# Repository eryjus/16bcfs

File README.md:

# 16-Bit Computer From Scratch

This repository contains the complete works associated with the 16-Bit Computer From Scrath (16bcfs) project.

---

## Videos

I am documenting my 16-Bit Computer build in video form.  You can find the entire playlist [here](https://www.youtube.com/playlist?list=PLUF7WfBe0k3g9wpTtg41QP3jl5y8T1aGV).

---

## License

See [LICENSE.md](LICENSE.md).

---

## Build System

I use `tup` as my primary build system.  I usually will wrap `tup` in `make` commands.  You can find `tup` [here](https://gittup.org/tup/).  I simply find `tup` to more reliable detect changed sources with less work.

### Qt6_DIR Environment Variable

The `Qt6_DIR` Environment Variable needs to point to the installation location of Qt6, for example `~/Qt/6.6.0/gcc_64/`.  Your installation location may be different, so copy-and-paste is not advised.

---

## EEPROM Programmer

I do not have a commercial EEPROM programmer.  I use the TommyPROM programmer.  You can find all the relevant information on TommyPROM [here](https://tomnisbet.github.io/TommyPROM/).  In Linux, I use `minicom` as the interface.  Hint: use `sudo minicom -s` to set up the defaults.

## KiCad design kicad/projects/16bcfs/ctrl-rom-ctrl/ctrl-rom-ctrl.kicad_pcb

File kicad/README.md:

# 16-Bit Computer From Scratch KiCad Library

This folder contains the KiCad files used in designing the PCBs.

---

## Videos

I am documenting my 16-Bit Computer build in video form.  You can find the entire playlist [here](https://www.youtube.com/playlist?list=PLUF7WfBe0k3g9wpTtg41QP3jl5y8T1aGV).

---

## License

See [LICENSE.md](../LICENSE.md).

---

## Fitness

Please understand that I do not represent or warranty that these schematics and PCB designs are fit for any purpose including the project for which they were intended.  I would hate for you to invest your own hard-earned money into something that may or may not work for you.  However, you are free to do what you wish with this stuff as stated in the [license](../LICENSE.md).  Just have fun with it.

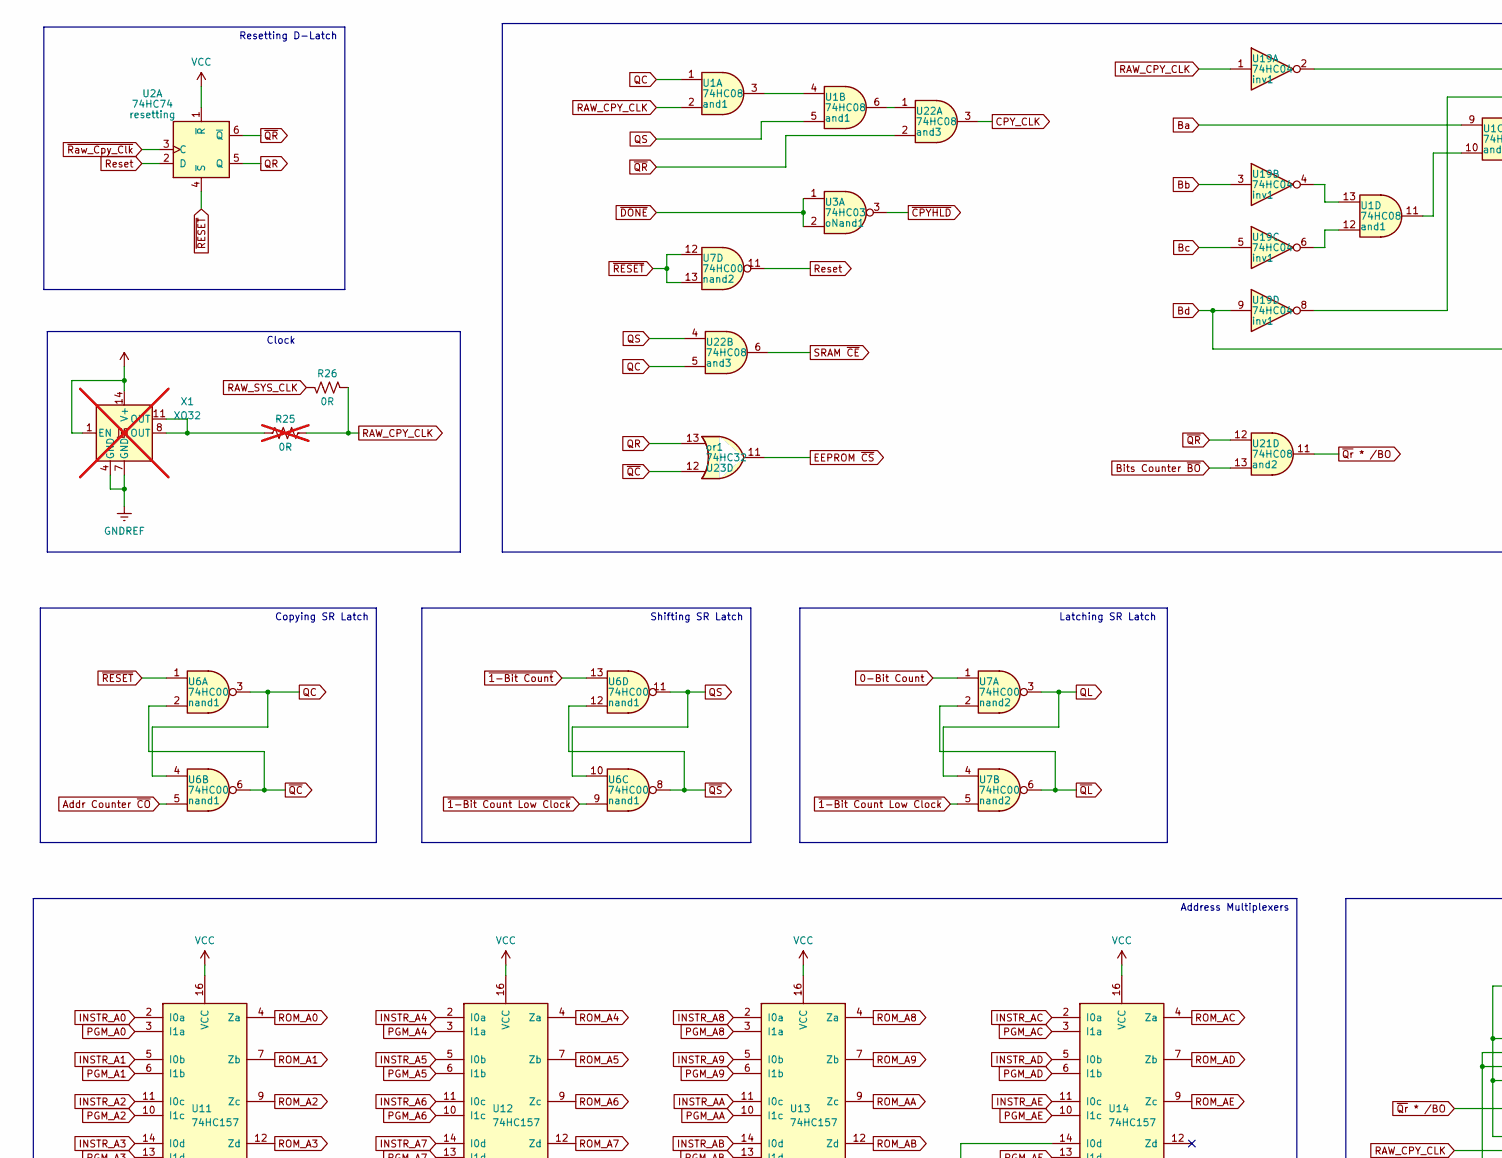
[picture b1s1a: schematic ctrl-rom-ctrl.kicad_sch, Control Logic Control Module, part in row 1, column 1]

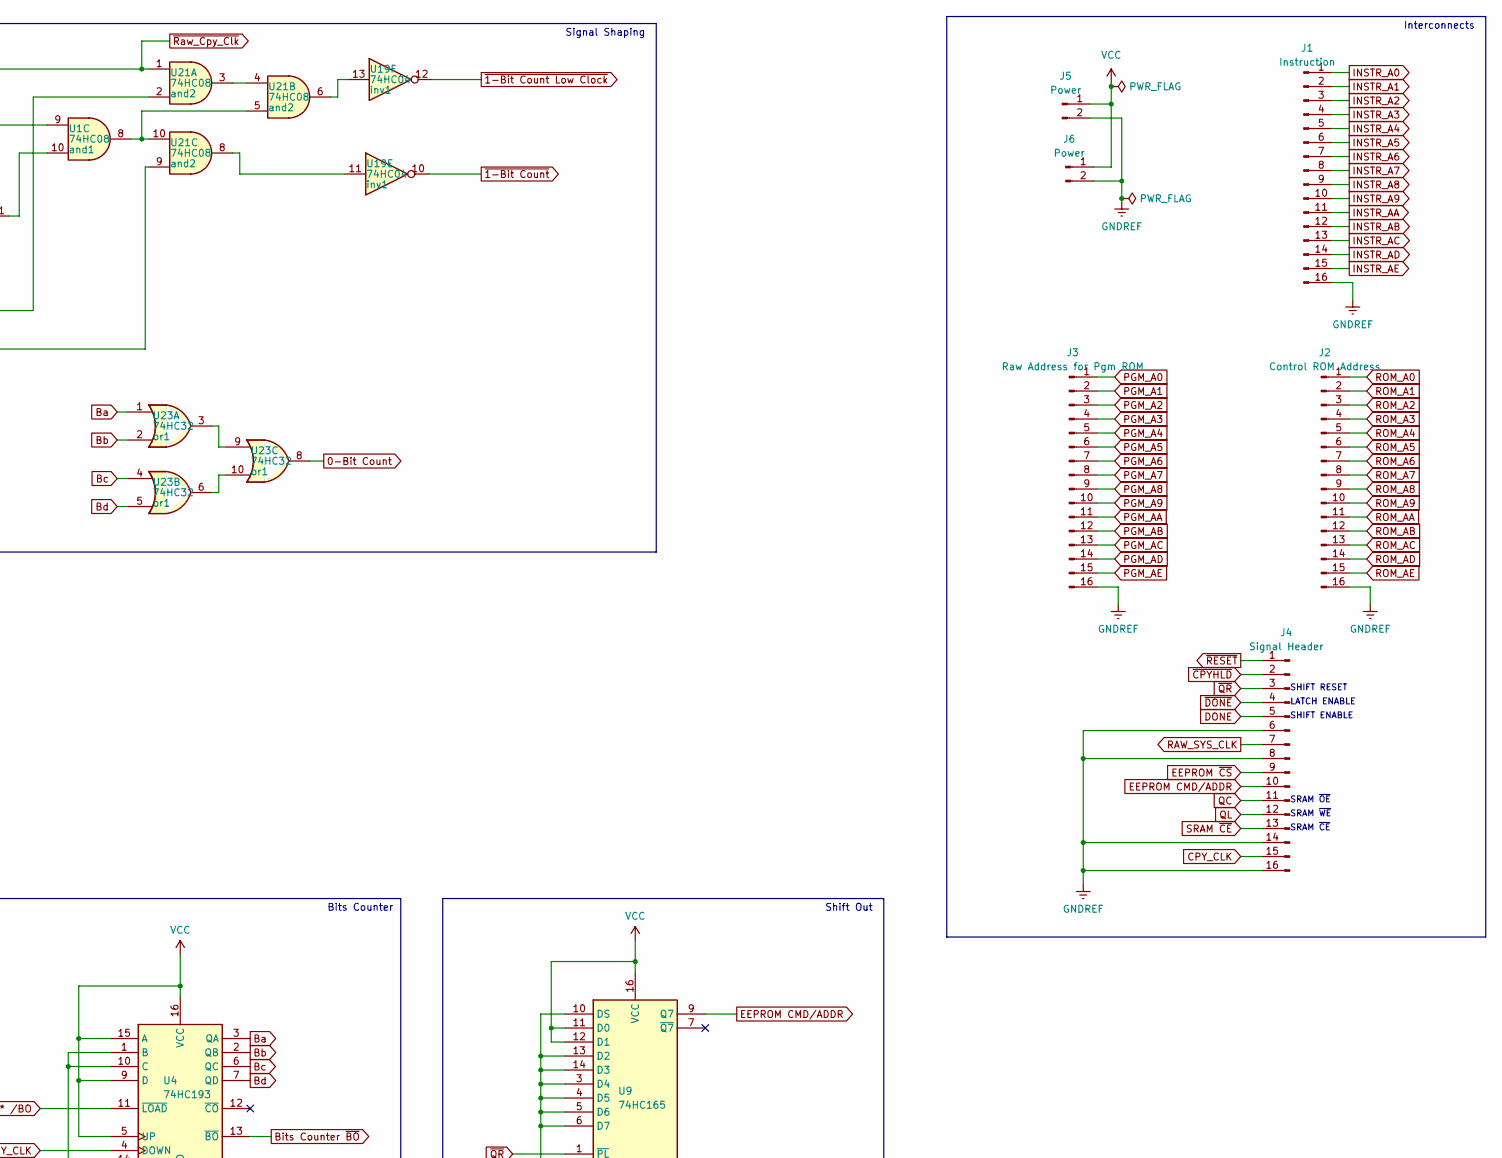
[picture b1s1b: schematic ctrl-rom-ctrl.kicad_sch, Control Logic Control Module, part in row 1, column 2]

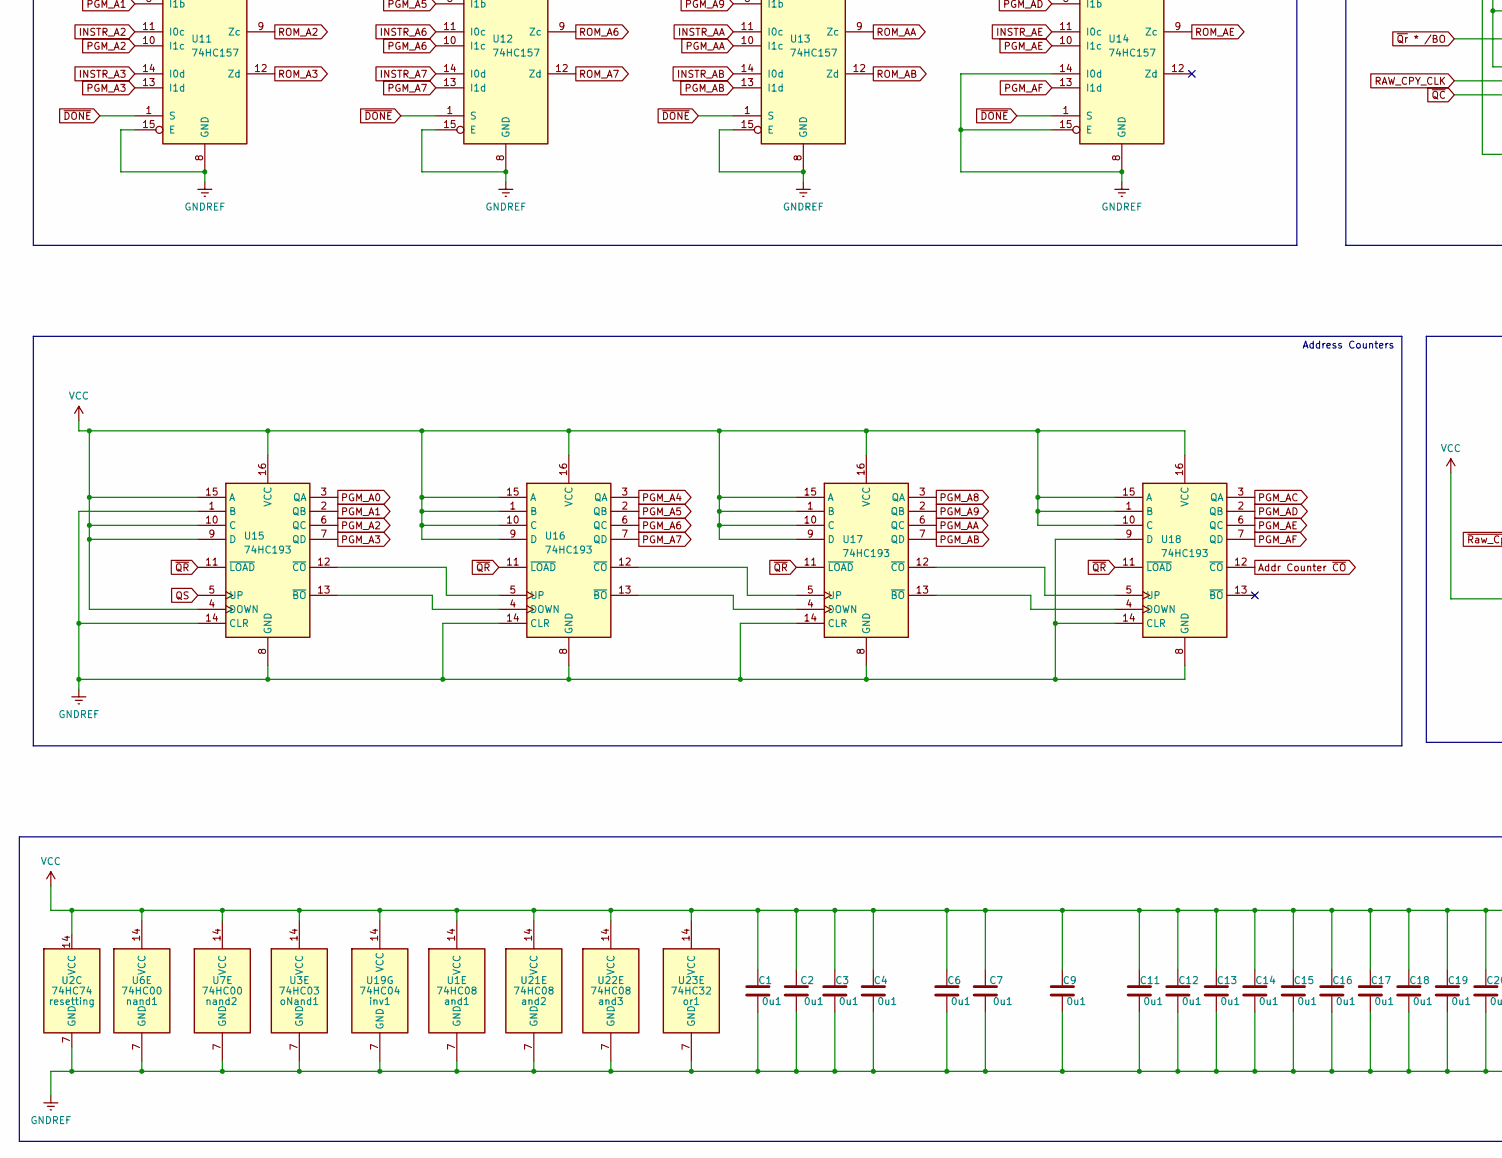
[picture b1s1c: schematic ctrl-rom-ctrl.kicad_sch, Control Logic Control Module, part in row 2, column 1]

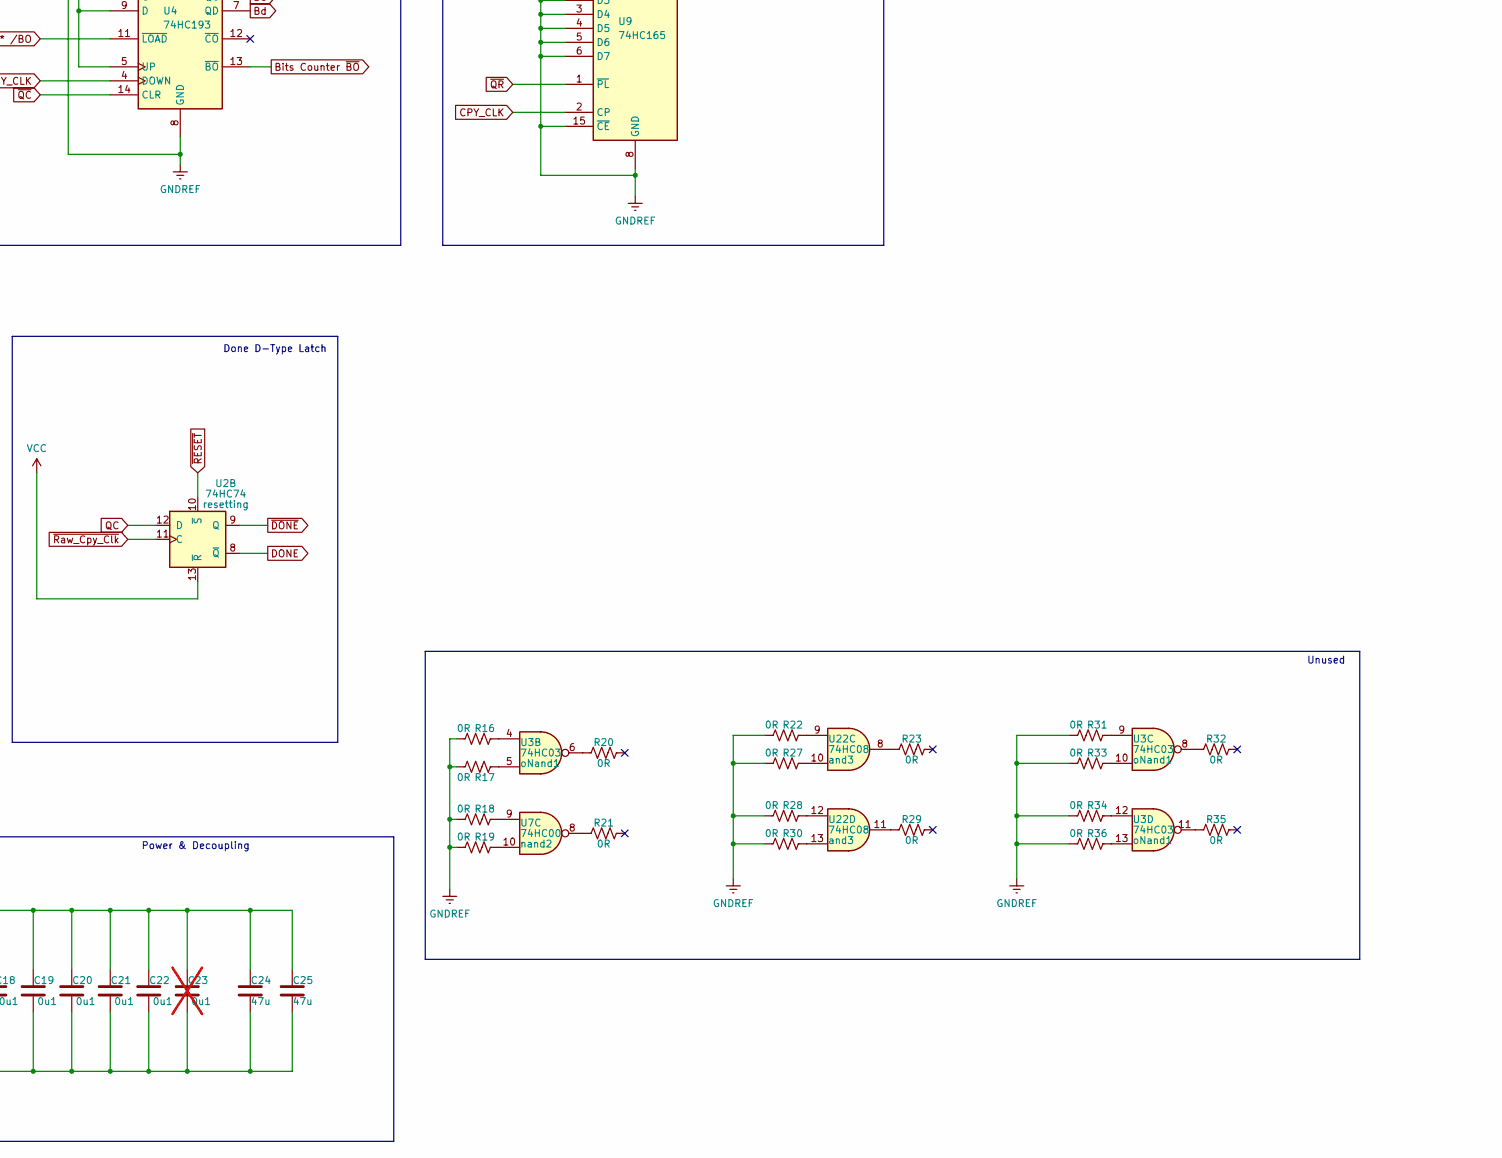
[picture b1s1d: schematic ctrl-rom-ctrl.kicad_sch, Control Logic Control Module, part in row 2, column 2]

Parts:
C1, C2, C3, C4, C6, C7, C9, C11, C12, C13, C14, C15, C16, C17, C18, C19, C20, C21, C22: 0u1; C_1206_3216Metric_Pad1.33x1.80mm_HandSolder
C23: 0u1; C_1206_3216Metric_Pad1.33x1.80mm_HandSolder; not fitted
C24, C25: 47u; C_1206_3216Metric_Pad1.33x1.80mm_HandSolder
J1: Instruction; PinHeader_1x16_P2.54mm_Vertical
J2: Control ROM Address; PinHeader_1x16_P2.54mm_Vertical
J3: Raw Address for Pgm ROM; PinHeader_1x16_P2.54mm_Vertical
J4: Signal Header; PinHeader_1x16_P2.54mm_Vertical
J5, J6: Power; PinHeader_1x02_P2.54mm_Vertical
R16, R17, R18, R19, R20, R21, R22, R23, R26, R27, R28, R29, R30, R31, R32, R33, R34, R35, R36: 0R; R_1206_3216Metric_Pad1.30x1.75mm_HandSolder
R25: 0R; R_1206_3216Metric_Pad1.30x1.75mm_HandSolder; not fitted
U1, U21, U22: 74HC08; SOIC-14_3.9x8.7mm_P1.27mm
U2: 74HC74; SOIC-14_3.9x8.7mm_P1.27mm
U3: 74HC03; SOIC-14_3.9x8.7mm_P1.27mm
U4, U15, U16, U17, U18: 74HC193; SOIC-16_3.9x9.9mm_P1.27mm
U6, U7: 74HC00; SOIC-14_3.9x8.7mm_P1.27mm
U9: 74HC165; SOIC-16_3.9x9.9mm_P1.27mm
U11, U12, U13, U14: 74HC157; SOIC-16_3.9x9.9mm_P1.27mm
U19: 74HC04; SOIC-14_3.9x8.7mm_P1.27mm
U23: 74HC32; SOIC-14_3.9x8.7mm_P1.27mm
X1: XO32; Oscillator_DIP-8-14; not fitted

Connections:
0-Bit Count: U7.1, U23.8
Addr Counter ~CO: U6.5, U18.12 (~CO)
Ba: U1.9, U4.3 (QA), U23.1
Bb: U4.2 (QB), U19.3, U23.2
Bc: U4.6 (QC), U19.5, U23.4
Bd: U4.7 (QD), U19.9, U21.9, U23.5
Bits Counter ~BO: U4.13 (~BO), U21.13
CPY_CLK: J4.15, U9.2 (CP), U22.3
DONE: J4.5, U2.8 (~Q)
EEPROM CMD/ADDR: J4.10, U9.9 (Q7)
EEPROM ~CS: J4.9, U23.11
GNDREF: C1.2, C2.2, C3.2, C4.2, C6.2, C7.2, C9.2, C11.2, C12.2, C13.2, C14.2, C15.2, C16.2, C17.2, C18.2, C19.2, C20.2, C21.2, C22.2, C23.2, C24.2, C25.2, J1.16, J2.16, J3.16, J4.6, J4.8, J4.14, J4.16, J5.2, J6.2, R16.1, R17.1, R18.1, R19.1, R22.1, R27.1, R28.1, R30.1, R31.1, R33.1, R34.1, R36.1, U1.7 (GND), U2.7 (GND), U3.7 (GND), U4.1 (B), U4.8 (GND), U4.10 (C), U6.7 (GND), U7.7 (GND), U9.3 (D4), U9.4 (D5), U9.5 (D6), U9.6 (D7), U9.8 (GND), U9.10 (DS), U9.13 (D2), U9.14 (D3), U9.15 (~CE), U11.8 (GND), U11.15 (E), U12.8 (GND), U12.15 (E), U13.8 (GND), U13.15 (E), U14.8 (GND), U14.14 (I0d), U14.15 (E), U15.1 (B), U15.8 (GND), U15.14 (CLR), U16.8 (GND), U16.14 (CLR), U17.8 (GND), U17.14 (CLR), U18.8 (GND), U18.9 (D), U18.14 (CLR), U19.7 (GND), U21.7 (GND), U22.7 (GND), U23.7 (GND), X1.4 (GND), X1.7 (GND)
INSTR_A0: J1.1, U11.2 (I0a)
INSTR_A1: J1.2, U11.5 (I0b)
INSTR_A2: J1.3, U11.11 (I0c)
INSTR_A3: J1.4, U11.14 (I0d)
INSTR_A4: J1.5, U12.2 (I0a)
INSTR_A5: J1.6, U12.5 (I0b)
INSTR_A6: J1.7, U12.11 (I0c)
INSTR_A7: J1.8, U12.14 (I0d)
INSTR_A8: J1.9, U13.2 (I0a)
INSTR_A9: J1.10, U13.5 (I0b)
INSTR_AA: J1.11, U13.11 (I0c)
INSTR_AB: J1.12, U13.14 (I0d)
INSTR_AC: J1.13, U14.2 (I0a)
INSTR_AD: J1.14, U14.5 (I0b)
INSTR_AE: J1.15, U14.11 (I0c)
unnamed: R16.2, U3.4
unnamed: R17.2, U3.5
unnamed: R18.2, U7.9
unnamed: R19.2, U7.10
unnamed: R20.1, U3.6
unnamed: R21.1, U7.8
unnamed: R22.2, U22.9
unnamed: R23.1, U22.8
unnamed: R25.1, X1.8 (OUT), X1.11 (OUT)
unnamed: R27.2, U22.10
unnamed: R28.2, U22.12
unnamed: R29.1, U22.11
unnamed: R30.2, U22.13
unnamed: R31.2, U3.9
unnamed: R32.1, U3.8
unnamed: R33.2, U3.10
unnamed: R34.2, U3.12
unnamed: R35.1, U3.11
unnamed: R36.2, U3.13
unnamed: U1.3, U1.4
unnamed: U1.6, U22.1
unnamed: U1.8, U21.5, U21.10
unnamed: U1.10, U1.11
unnamed: U1.12, U19.6
unnamed: U1.13, U19.4
unnamed: U15.13 (~BO), U16.4 (DOWN)
unnamed: U15.12 (~CO), U16.5 (UP)
unnamed: U16.13 (~BO), U17.4 (DOWN)
unnamed: U16.12 (~CO), U17.5 (UP)
unnamed: U17.13 (~BO), U18.4 (DOWN)
unnamed: U17.12 (~CO), U18.5 (UP)
unnamed: U19.8, U21.2
unnamed: U19.11, U21.8
unnamed: U19.13, U21.6
unnamed: U21.3, U21.4
unnamed: U23.3, U23.9
unnamed: U23.6, U23.10
PGM_A0: J3.1, U11.3 (I1a), U15.3 (QA)
PGM_A1: J3.2, U11.6 (I1b), U15.2 (QB)
PGM_A2: J3.3, U11.10 (I1c), U15.6 (QC)
PGM_A3: J3.4, U11.13 (I1d), U15.7 (QD)
PGM_A4: J3.5, U12.3 (I1a), U16.3 (QA)
PGM_A5: J3.6, U12.6 (I1b), U16.2 (QB)
PGM_A6: J3.7, U12.10 (I1c), U16.6 (QC)
PGM_A7: J3.8, U12.13 (I1d), U16.7 (QD)
PGM_A8: J3.9, U13.3 (I1a), U17.3 (QA)
PGM_A9: J3.10, U13.6 (I1b), U17.2 (QB)
PGM_AA: J3.11, U13.10 (I1c), U17.6 (QC)
PGM_AB: J3.12, U13.13 (I1d), U17.7 (QD)
PGM_AC: J3.13, U14.3 (I1a), U18.3 (QA)
PGM_AD: J3.14, U14.6 (I1b), U18.2 (QB)
PGM_AE: J3.15, U14.10 (I1c), U18.6 (QC)
PGM_AF: U14.13 (I1d), U18.7 (QD)
QC: J4.11, U1.1, U2.12 (D), U6.3, U6.4, U22.5
QL: J4.12, U7.3, U7.4
QR: U2.5 (Q), U23.13
QS: U1.5, U6.10, U6.11, U15.5 (UP), U22.4
RAW_CPY_CLK: R25.2, R26.1, U1.2, U4.4 (DOWN), U19.1
RAW_SYS_CLK: J4.7, R26.2
ROM_A0: J2.1, U11.4 (Za)
ROM_A1: J2.2, U11.7 (Zb)
ROM_A2: J2.3, U11.9 (Zc)
ROM_A3: J2.4, U11.12 (Zd)
ROM_A4: J2.5, U12.4 (Za)
ROM_A5: J2.6, U12.7 (Zb)
ROM_A6: J2.7, U12.9 (Zc)
ROM_A7: J2.8, U12.12 (Zd)
ROM_A8: J2.9, U13.4 (Za)
ROM_A9: J2.10, U13.7 (Zb)
ROM_AA: J2.11, U13.9 (Zc)
ROM_AB: J2.12, U13.12 (Zd)
ROM_AC: J2.13, U14.4 (Za)
ROM_AD: J2.14, U14.7 (Zb)
ROM_AE: J2.15, U14.9 (Zc)
Reset: U2.2 (D), U7.11
SRAM ~CE: J4.13, U22.6
VCC: C1.1, C2.1, C3.1, C4.1, C6.1, C7.1, C9.1, C11.1, C12.1, C13.1, C14.1, C15.1, C16.1, C17.1, C18.1, C19.1, C20.1, C21.1, C22.1, C23.1, C24.1, C25.1, J5.1, J6.1, U1.14 (VCC), U2.1 (~R), U2.13 (~R), U2.14 (VCC), U3.14 (VCC), U4.5 (UP), U4.9 (D), U4.15 (A), U4.16 (VCC), U6.14 (VCC), U7.14 (VCC), U9.11 (D0), U9.12 (D1), U9.16 (VCC), U11.16 (VCC), U12.16 (VCC), U13.16 (VCC), U14.16 (VCC), U15.4 (DOWN), U15.9 (D), U15.10 (C), U15.15 (A), U15.16 (VCC), U16.1 (B), U16.9 (D), U16.10 (C), U16.15 (A), U16.16 (VCC), U17.1 (B), U17.9 (D), U17.10 (C), U17.15 (A), U17.16 (VCC), U18.1 (B), U18.10 (C), U18.15 (A), U18.16 (VCC), U19.14 (VCC), U21.14 (VCC), U22.14 (VCC), U23.14 (VCC), X1.1 (EN), X1.14 (V+)
~1-Bit Count Low Clock: U6.9, U7.5, U19.12
~1-Bit Count: U6.13, U19.10
~CPYHLD: J4.2, U3.3
~DONE: J4.4, U2.9 (Q), U3.1, U3.2, U11.1 (S), U12.1 (S), U13.1 (S), U14.1 (S)
~QC: U4.14 (CLR), U6.2, U6.6, U23.12
~QL: U7.2, U7.6
~QR: J4.3, U2.6 (~Q), U9.1 (~PL), U15.11 (~LOAD), U16.11 (~LOAD), U17.11 (~LOAD), U18.11 (~LOAD), U21.12, U22.2
~QS: U6.8, U6.12
~Qr * /BO: U4.11 (~LOAD), U21.11
~RESET: J4.1, U2.4 (~S), U2.10 (~S), U6.1, U7.12, U7.13
~Raw_Cpy_Clk: U2.3 (C), U2.11 (C), U19.2, U21.1

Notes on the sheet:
SHIFT RESET
Shift Out
Shifting SR Latch
Resetting D-Latch
LATCH ENABLE
Clock
SRAM ~{CE}
SRAM ~{WE}
Bits Counter
Unused
Power & Decoupling
Copying SR Latch
SRAM ~{OE}
Address Multiplexers
Done D-Type Latch
SHIFT ENABLE
Address Counters
Signal Shaping
Interconnects
Latching SR Latch

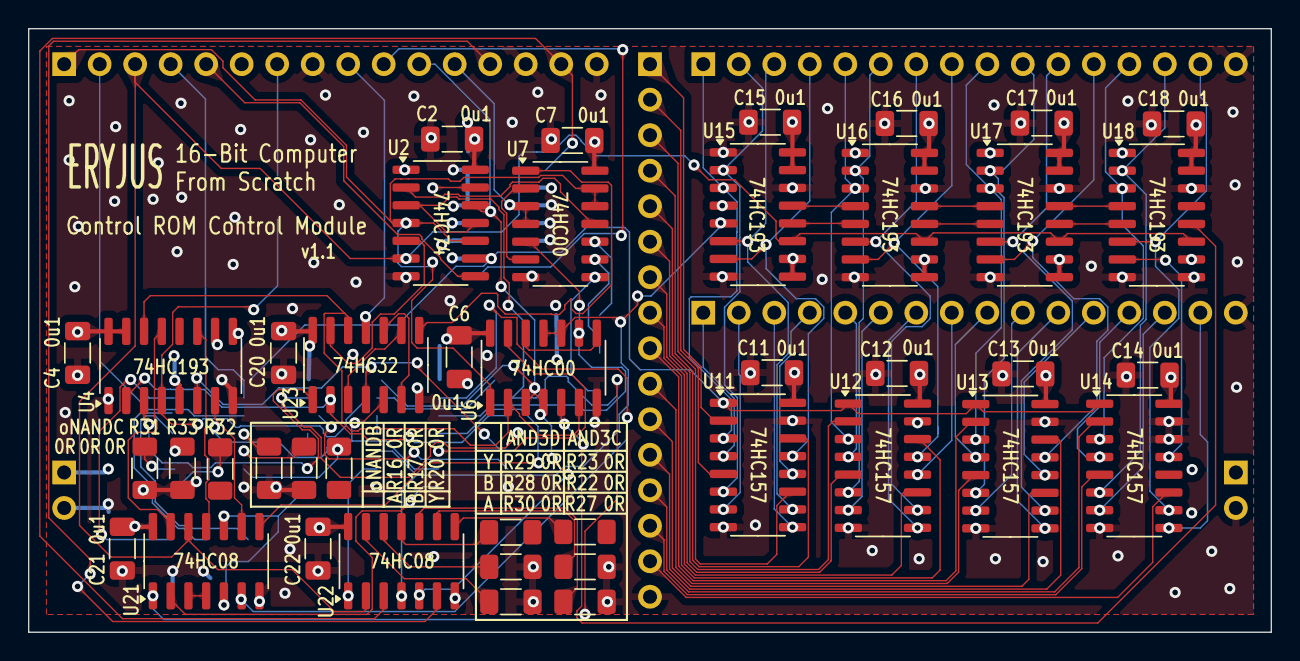
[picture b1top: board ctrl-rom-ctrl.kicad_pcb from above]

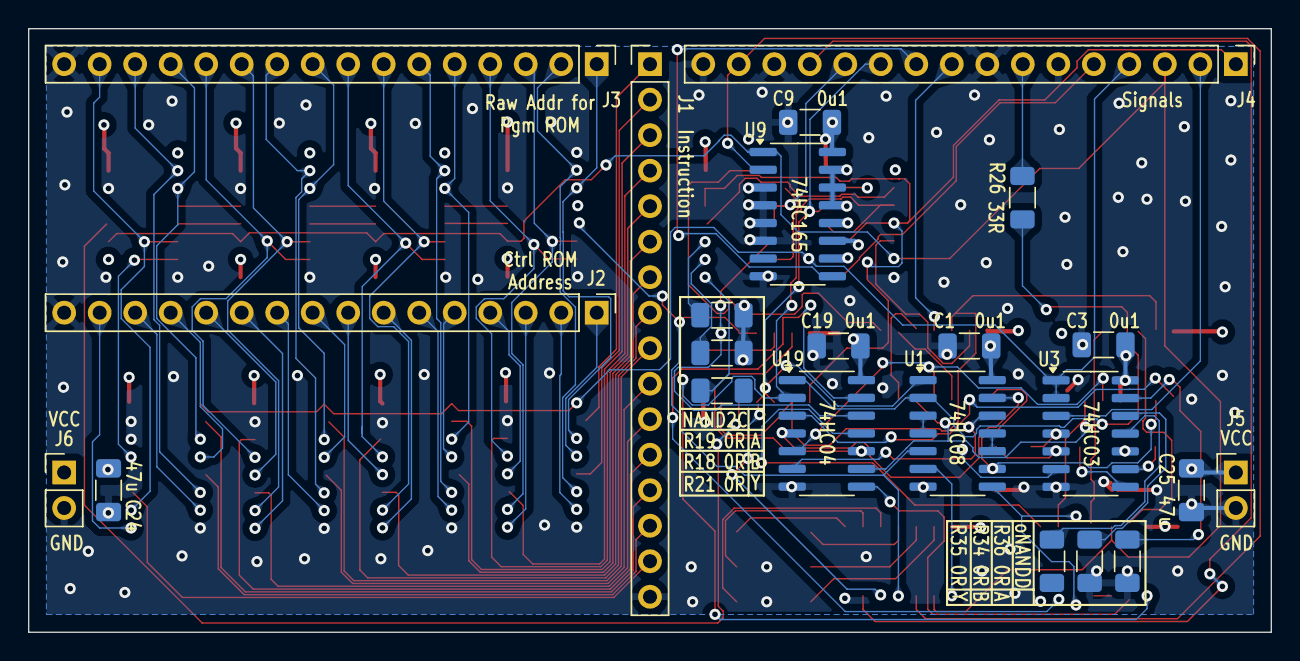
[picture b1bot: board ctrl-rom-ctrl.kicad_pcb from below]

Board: 4 copper layers, 88.9 x 43.2 mm, 65 parts (23 on the bottom side), 114 nets.

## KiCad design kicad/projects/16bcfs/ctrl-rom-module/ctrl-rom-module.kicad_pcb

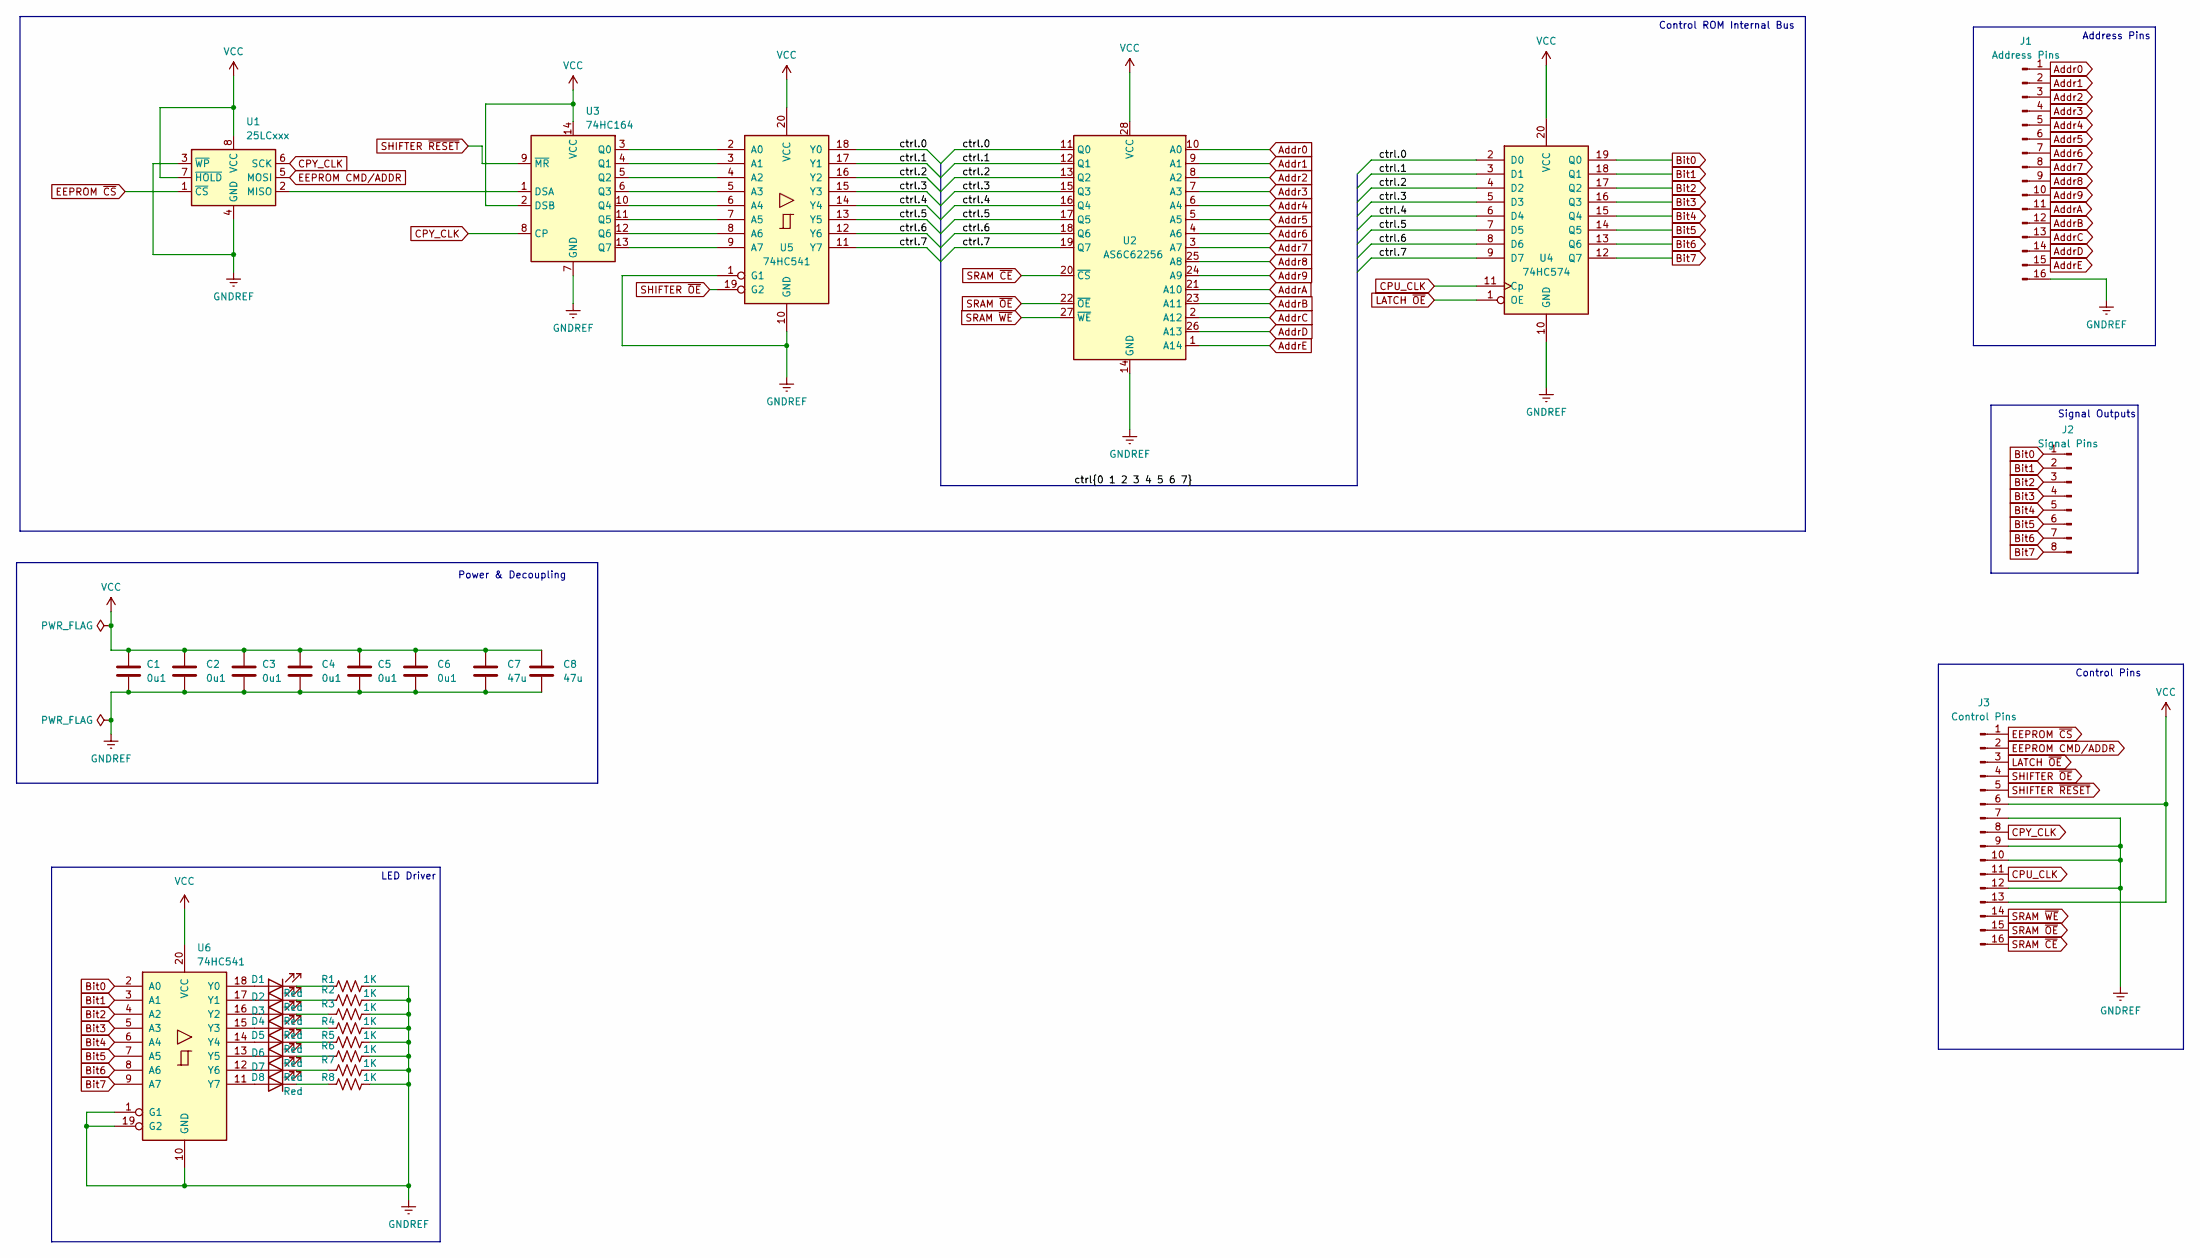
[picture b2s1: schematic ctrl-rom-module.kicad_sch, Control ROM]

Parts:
C1, C2, C3, C4, C5, C6: 0u1; C_1206_3216Metric_Pad1.33x1.80mm_HandSolder
C7, C8: 47u; C_1206_3216Metric_Pad1.33x1.80mm_HandSolder
D1, D2, D3, D4, D5, D6, D7, D8: Red; LED_1206_3216Metric_Pad1.42x1.75mm_HandSolder
J1: Address Pins; PinHeader_1x16_P2.54mm_Vertical
J2: Signal Pins; PinHeader_1x08_P2.54mm_Vertical
J3: Control Pins; PinHeader_1x16_P2.54mm_Vertical
R1, R2, R3, R4, R5, R6, R7, R8: 1K; R_1206_3216Metric_Pad1.30x1.75mm_HandSolder
U1: 25LCxxx; DIP-8_W7.62mm_Socket
U2: AS6C62256; SOP-28_MIL330_ALL
U3: 74HC164; SOIC-14_3.9x8.7mm_P1.27mm
U4: 74HC574; SOIC-20W_7.5x12.8mm_P1.27mm
U5, U6: 74HC541; SOIC-20W_7.5x12.8mm_P1.27mm

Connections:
/ctrl.0: U2.11 (Q0), U4.2 (D0), U5.18 (Y0)
/ctrl.1: U2.12 (Q1), U4.3 (D1), U5.17 (Y1)
/ctrl.2: U2.13 (Q2), U4.4 (D2), U5.16 (Y2)
/ctrl.3: U2.15 (Q3), U4.5 (D3), U5.15 (Y3)
/ctrl.4: U2.16 (Q4), U4.6 (D4), U5.14 (Y4)
/ctrl.5: U2.17 (Q5), U4.7 (D5), U5.13 (Y5)
/ctrl.6: U2.18 (Q6), U4.8 (D6), U5.12 (Y6)
/ctrl.7: U2.19 (Q7), U4.9 (D7), U5.11 (Y7)
Addr0: J1.1, U2.10 (A0)
Addr1: J1.2, U2.9 (A1)
Addr2: J1.3, U2.8 (A2)
Addr3: J1.4, U2.7 (A3)
Addr4: J1.5, U2.6 (A4)
Addr5: J1.6, U2.5 (A5)
Addr6: J1.7, U2.4 (A6)
Addr7: J1.8, U2.3 (A7)
Addr8: J1.9, U2.25 (A8)
Addr9: J1.10, U2.24 (A9)
AddrA: J1.11, U2.21 (A10)
AddrB: J1.12, U2.23 (A11)
AddrC: J1.13, U2.2 (A12)
AddrD: J1.14, U2.26 (A13)
AddrE: J1.15, U2.1 (A14)
Bit0: J2.1, U4.19 (Q0), U6.2 (A0)
Bit1: J2.2, U4.18 (Q1), U6.3 (A1)
Bit2: J2.3, U4.17 (Q2), U6.4 (A2)
Bit3: J2.4, U4.16 (Q3), U6.5 (A3)
Bit4: J2.5, U4.15 (Q4), U6.6 (A4)
Bit5: J2.6, U4.14 (Q5), U6.7 (A5)
Bit6: J2.7, U4.13 (Q6), U6.8 (A6)
Bit7: J2.8, U4.12 (Q7), U6.9 (A7)
CPU_CLK: J3.11, U4.11 (Cp)
CPY_CLK: J3.8, U1.6 (SCK), U3.8 (CP)
EEPROM CMD/ADDR: J3.2, U1.5 (MOSI)
EEPROM ~CS: J3.1, U1.1 (~CS)
GNDREF: C1.2, C2.2, C3.2, C4.2, C5.2, C6.2, C7.2, C8.2, J1.16, J3.7, J3.9, J3.10, J3.12, R1.2, R2.2, R3.2, R4.2, R5.2, R6.2, R7.2, R8.2, U1.3 (~WP), U1.4 (GND), U2.14 (GND), U3.7 (GND), U4.10 (GND), U5.1 (G1), U5.10 (GND), U6.1 (G1), U6.10 (GND), U6.19 (G2)
LATCH ~OE: J3.3, U4.1 (OE)
unnamed: D1.2 (A), U6.18 (Y0)
unnamed: D1.1 (K), R1.1
unnamed: D2.2 (A), U6.17 (Y1)
unnamed: D2.1 (K), R2.1
unnamed: D3.2 (A), U6.16 (Y2)
unnamed: D3.1 (K), R3.1
unnamed: D4.2 (A), U6.15 (Y3)
unnamed: D4.1 (K), R4.1
unnamed: D5.2 (A), U6.14 (Y4)
unnamed: D5.1 (K), R5.1
unnamed: D6.2 (A), U6.13 (Y5)
unnamed: D6.1 (K), R6.1
unnamed: D7.2 (A), U6.12 (Y6)
unnamed: D7.1 (K), R7.1
unnamed: D8.2 (A), U6.11 (Y7)
unnamed: D8.1 (K), R8.1
unnamed: U1.2 (MISO), U3.1 (DSA)
unnamed: U3.3 (Q0), U5.2 (A0)
unnamed: U3.4 (Q1), U5.3 (A1)
unnamed: U3.5 (Q2), U5.4 (A2)
unnamed: U3.6 (Q3), U5.5 (A3)
unnamed: U3.10 (Q4), U5.6 (A4)
unnamed: U3.11 (Q5), U5.7 (A5)
unnamed: U3.12 (Q6), U5.8 (A6)
unnamed: U3.13 (Q7), U5.9 (A7)
SHIFTER ~OE: J3.4, U5.19 (G2)
SHIFTER ~RESET: J3.5, U3.9 (~MR)
SRAM ~CE: J3.16, U2.20 (~CS)
SRAM ~OE: J3.15, U2.22 (~OE)
SRAM ~WE: J3.14, U2.27 (~WE)
VCC: C1.1, C2.1, C3.1, C4.1, C5.1, C6.1, C7.1, C8.1, J3.6, J3.13, U1.7 (~HOLD), U1.8 (VCC), U2.28 (VCC), U3.2 (DSB), U3.14 (VCC), U4.20 (VCC), U5.20 (VCC), U6.20 (VCC)

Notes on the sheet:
Control ROM Internal Bus
Address Pins
Signal Outputs
Power & Decoupling
Control Pins
LED Driver

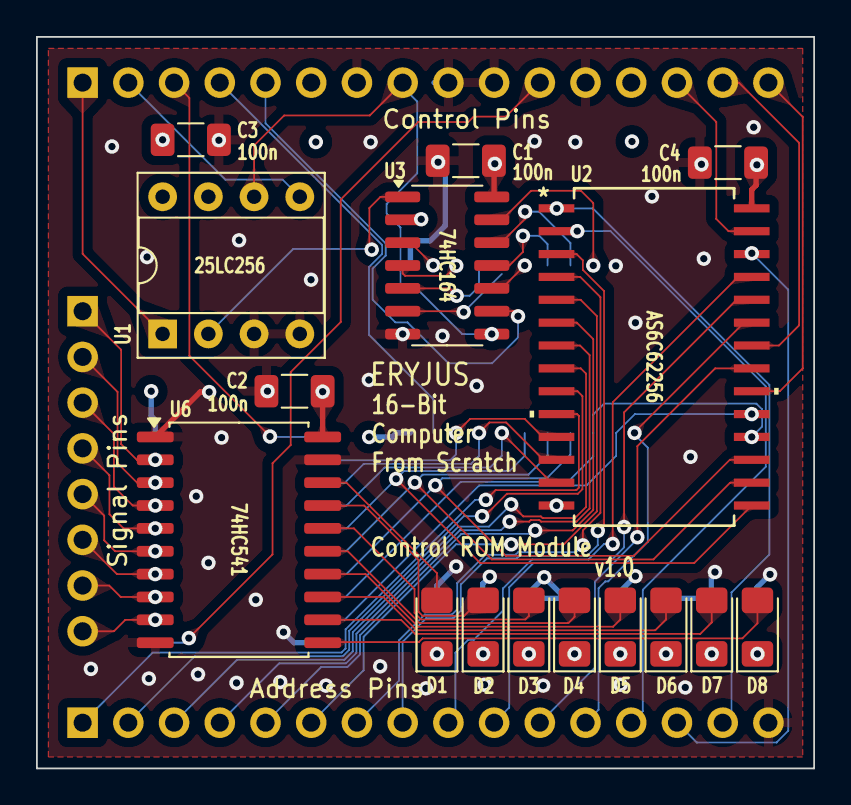
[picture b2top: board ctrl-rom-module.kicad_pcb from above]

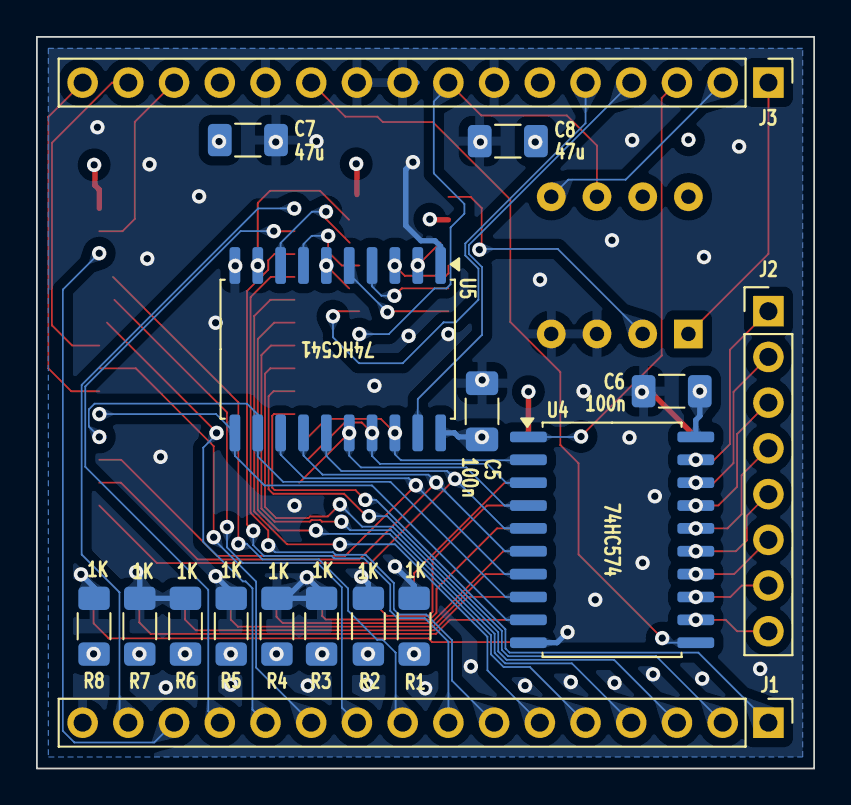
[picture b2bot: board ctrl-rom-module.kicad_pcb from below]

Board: 4 copper layers, 43.2 x 40.6 mm, 33 parts (17 on the bottom side), 68 nets.

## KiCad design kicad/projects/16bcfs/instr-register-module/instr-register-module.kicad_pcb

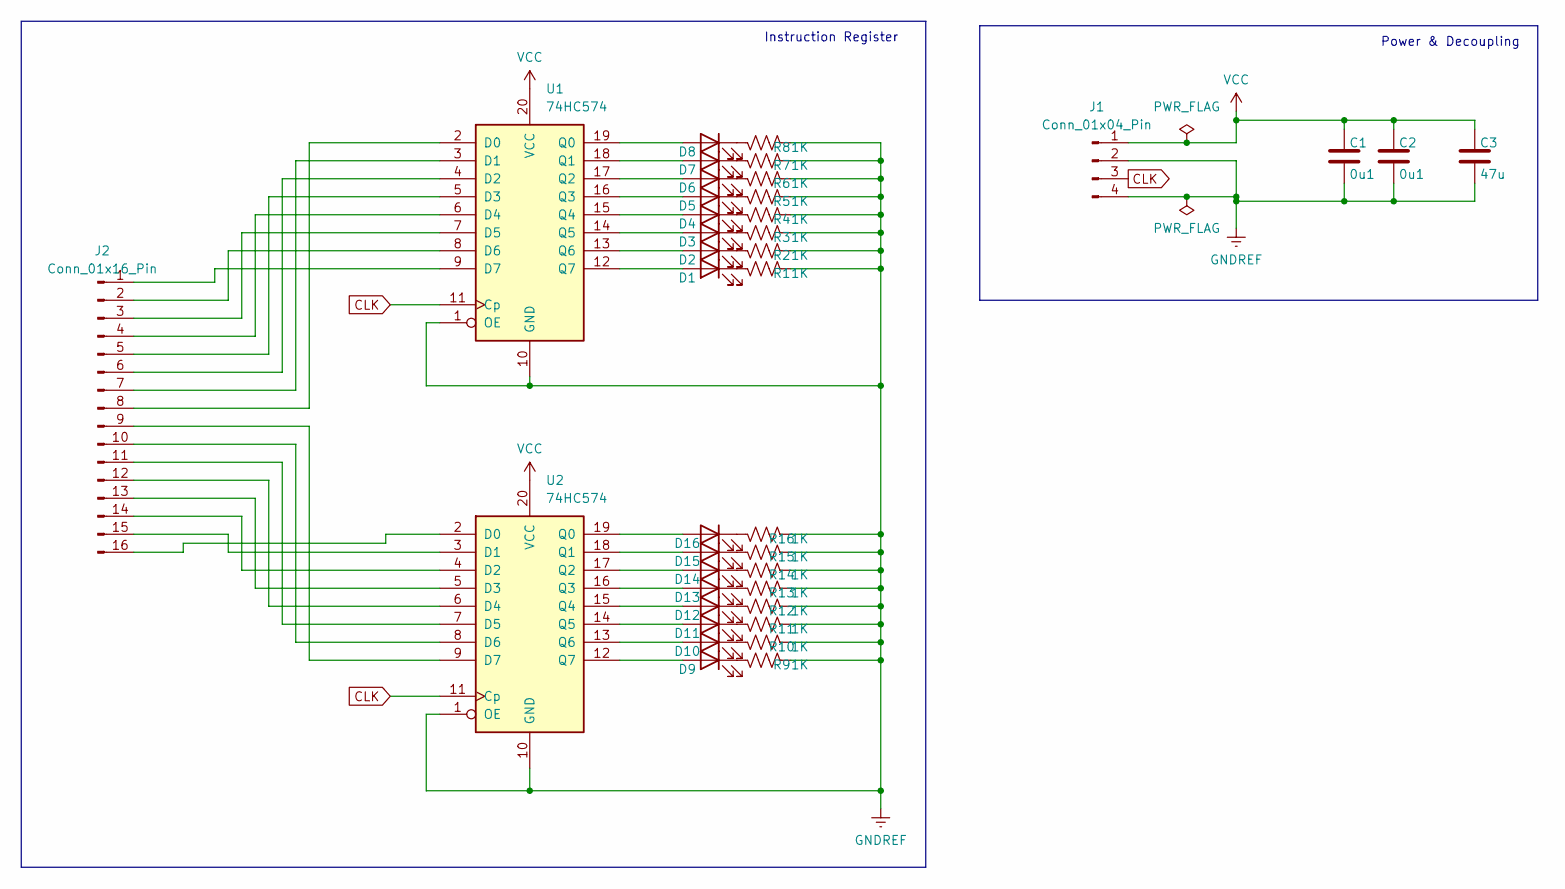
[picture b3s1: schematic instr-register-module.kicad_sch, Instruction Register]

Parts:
C1, C2: 0u1; C_1206_3216Metric_Pad1.33x1.80mm_HandSolder
C3: 47u; C_1206_3216Metric_Pad1.33x1.80mm_HandSolder
D1, D2, D3, D4, D5, D6, D7, D8, D9, D10, D11, D12, D13, D14, D15, D16: LED; LED_1206_3216Metric_Pad1.42x1.75mm_HandSolder
J1: Conn_01x04_Pin; PinHeader_1x04_P2.54mm_Vertical
J2: Conn_01x16_Pin; PinHeader_1x16_P2.54mm_Vertical
R1, R2, R3, R4, R5, R6, R7, R8, R9, R10, R11, R12, R13, R14, R15, R16: 1K; R_1206_3216Metric_Pad1.30x1.75mm_HandSolder
U1, U2: 74HC574; SOIC-20W_7.5x12.8mm_P1.27mm

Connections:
CLK: J1.3, U1.11 (Cp), U2.11 (Cp)
GNDREF: C1.2, C2.2, C3.2, J1.2, J1.4, R1.2, R2.2, R3.2, R4.2, R5.2, R6.2, R7.2, R8.2, R9.2, R10.2, R11.2, R12.2, R13.2, R14.2, R15.2, R16.2, U1.1 (OE), U1.10 (GND), U2.1 (OE), U2.10 (GND)
unnamed: D1.2 (A), U1.12 (Q7)
unnamed: D1.1 (K), R1.1
unnamed: D2.2 (A), U1.13 (Q6)
unnamed: D2.1 (K), R2.1
unnamed: D3.2 (A), U1.14 (Q5)
unnamed: D3.1 (K), R3.1
unnamed: D4.2 (A), U1.15 (Q4)
unnamed: D4.1 (K), R4.1
unnamed: D5.2 (A), U1.16 (Q3)
unnamed: D5.1 (K), R5.1
unnamed: D6.2 (A), U1.17 (Q2)
unnamed: D6.1 (K), R6.1
unnamed: D7.2 (A), U1.18 (Q1)
unnamed: D7.1 (K), R7.1
unnamed: D8.2 (A), U1.19 (Q0)
unnamed: D8.1 (K), R8.1
unnamed: D9.2 (A), U2.12 (Q7)
unnamed: D9.1 (K), R9.1
unnamed: D10.2 (A), U2.13 (Q6)
unnamed: D10.1 (K), R10.1
unnamed: D11.2 (A), U2.14 (Q5)
unnamed: D11.1 (K), R11.1
unnamed: D12.2 (A), U2.15 (Q4)
unnamed: D12.1 (K), R12.1
unnamed: D13.2 (A), U2.16 (Q3)
unnamed: D13.1 (K), R13.1
unnamed: D14.2 (A), U2.17 (Q2)
unnamed: D14.1 (K), R14.1
unnamed: D15.2 (A), U2.18 (Q1)
unnamed: D15.1 (K), R15.1
unnamed: D16.2 (A), U2.19 (Q0)
unnamed: D16.1 (K), R16.1
unnamed: J2.1, U1.9 (D7)
unnamed: J2.2, U1.8 (D6)
unnamed: J2.3, U1.7 (D5)
unnamed: J2.4, U1.6 (D4)
unnamed: J2.5, U1.5 (D3)
unnamed: J2.6, U1.4 (D2)
unnamed: J2.7, U1.3 (D1)
unnamed: J2.8, U1.2 (D0)
unnamed: J2.9, U2.9 (D7)
unnamed: J2.10, U2.8 (D6)
unnamed: J2.11, U2.7 (D5)
unnamed: J2.12, U2.6 (D4)
unnamed: J2.13, U2.5 (D3)
unnamed: J2.14, U2.4 (D2)
unnamed: J2.15, U2.3 (D1)
unnamed: J2.16, U2.2 (D0)
VCC: C1.1, C2.1, C3.1, J1.1, U1.20 (VCC), U2.20 (VCC)

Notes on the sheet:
Power & Decoupling
Instruction Register
